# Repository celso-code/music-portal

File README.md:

# music-portal
- this is a project made for the fallout project on hack club, its called **music portal**. It is a (semi) 1 to 1 replica of the radio from the game portal, but its not just a replica, it is also a **fully functional FM radio AND a blutetooth speaker**, hence the name music portal .
- How do you build it ? Its pretty easy so the pcb fits in a slot in the black base part, and so does the black lid, the withe upper part has holes to intall 3 nuts which are also in the base, so just aling them, use a solder iron the place the nuts in each hole and use screws to join them together
- The way you use it pretty intuitive, theres a switch in the back to choose betweeen off, fm radio, and bluetooth, then theres two knobs, one to control the radio station if you're on radio mode and the other to control the volume.
- Its powwered by an ESP32 for the main control, for the fm functions it uses the fm radio module RDA5807 with a simple amplifier circuit for the speaker, and the it uses the MAX98357 as  DAC (digital to analog converter) for the bluetooth speaker mode.
- My reason to build this project is because portal is one of my favourite games oat and since the radio is one of the most iconic "symbols" of the game  I think it would be pretty cool to have it as physical object that also has a real purpose and utility. 
- I also tough it would be a cool way to learn certain skills  like cad modelling and pcb design 
heres a few photos of the project

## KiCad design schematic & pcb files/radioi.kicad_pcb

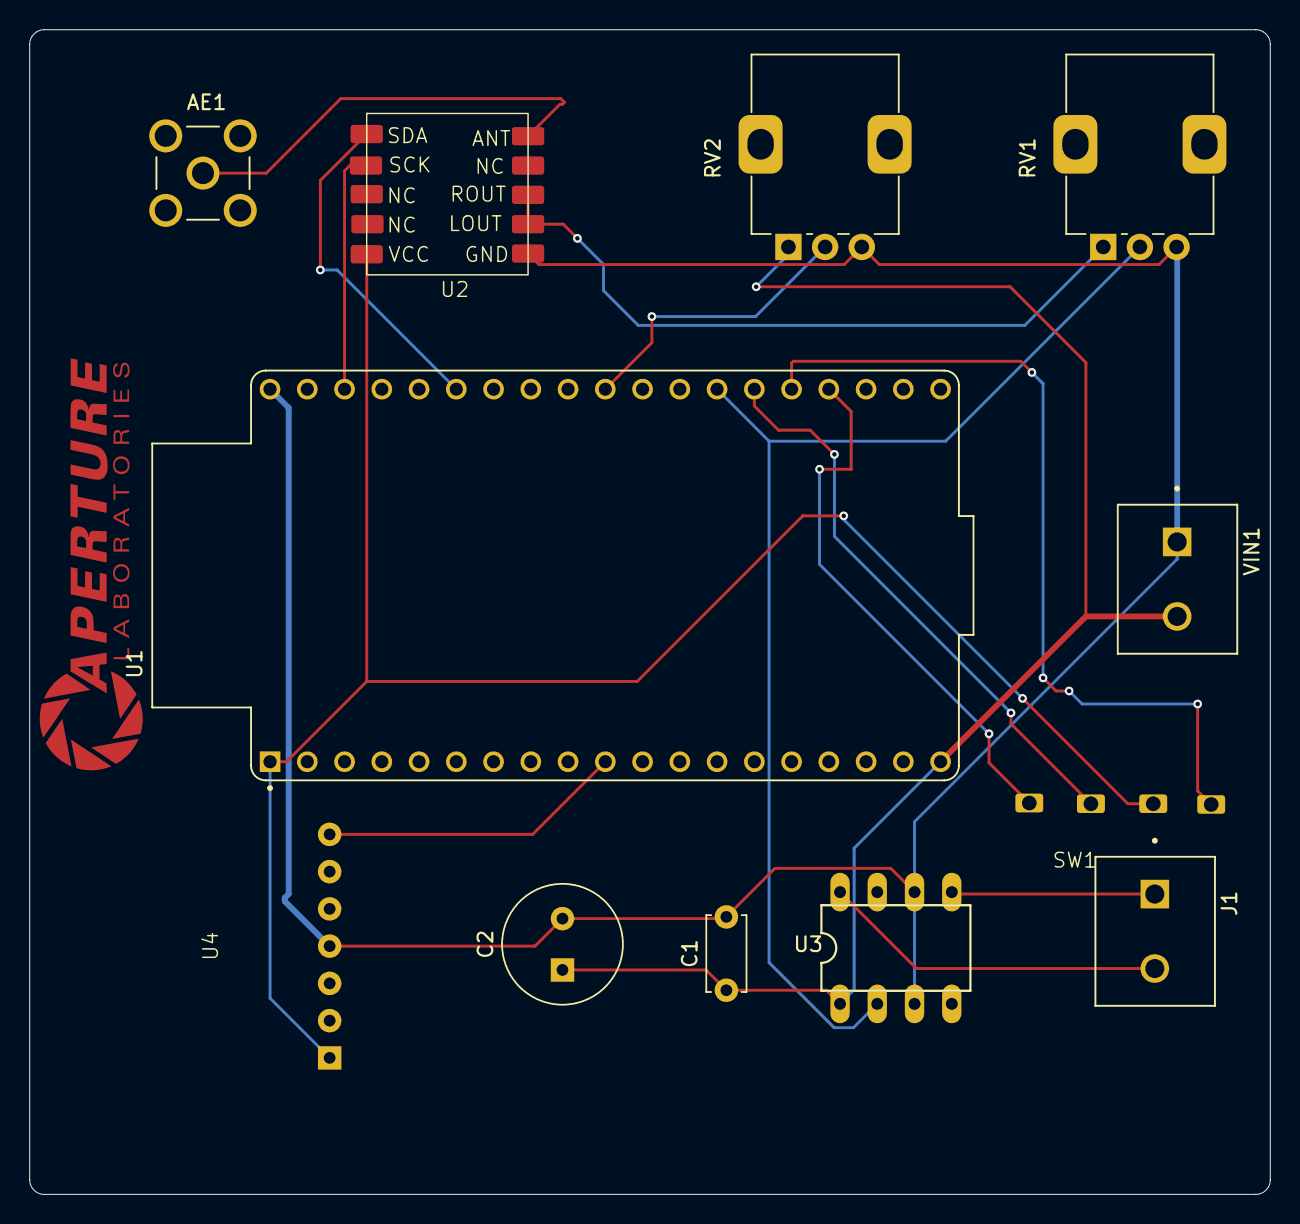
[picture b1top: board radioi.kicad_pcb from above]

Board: 2 copper layers, 84.6 x 79.4 mm, 12 parts (0 on the bottom side), 15 nets.

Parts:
AE1: Antenna; HUBER_SUHNER_82_SMA-50-0-41_133_NE
C1: 1uf; C_Disc_D5.0mm_W2.5mm_P5.00mm
C2: 100uF; C_Radial_D8.0mm_H11.5mm_P3.50mm_polar
J1: 1729128; PHOENIX_1729128
RV1: 5K; Potentiometer_Alps_RK09K_Single_Vertical
RV2: 5v; Potentiometer_Alps_RK09K_Single_Vertical
SW1: SW_DP3T; DP3T
U1: ESP32-DEVKITC-32E; MODULE_ESP32-DEVKITC-32E
U2: RDA5807M; RDA5807M-MY
U3: TDA7052A; DIL08
U4: MAX98357A; MAX98357
VIN1: 1729128; PHOENIX_1729128

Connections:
unnamed: AE1.1 (A), U2.6 (ANT)
unnamed: J1.1, U3.5
unnamed: J1.2, U3.8
unnamed: SW1.3, U1.J2_1 (3V3), U2.5 (VCC), U4.8 (VDD)
unnamed: C1.1, C2.1, RV2.1, U1.J2_19 (EXT_5V), U3.1 (VP), VIN1.2
unnamed: C1.2, C2.2, RV1.3, RV2.3, U1.J3_1 (GND_J3_1), U2.10 (GND), U3.3 (GND), U3.6 (GND), U4.11 (GND)
unnamed: SW1.2, U1.J3_14 (IO0)
unnamed: SW1.4, U1.J3_15 (IO2)
unnamed: RV1.2, U1.J3_13 (IO4), U3.2 (+)
unnamed: RV2.2, U1.J3_10 (IO5)
unnamed: SW1.1, U1.J3_16 (IO15)
unnamed: U1.J3_6 (IO21), U2.1 (SCA)
unnamed: U1.J3_3 (IO22), U2.4 (SCR)
unnamed: U1.J2_10 (IO26), U4.14 (LRCLK)
unnamed: RV1.1, U2.8 (LO), U2.9 (RO)

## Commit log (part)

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2026-05-13 Enhance README with project details and images
    Expanded project description with details about functionality, components, and personal motivation. Added images and schematic for better understanding.
2026-05-13 Refactor Arduino code with improved comments
    Updated comments for clarity and added missing include.
2026-05-13 pcb files
    these are the step and gerber files for the pcb
2026-05-17 Create 3D print files
2026-05-17 3d printable files
    these are the files for the 3d print
2026-05-21 Create temp
2026-05-21 Create t
2026-05-21 these files are to 3d print (duhh)
2026-05-21 Gerber Step an schematic
2026-05-21 Revise README with project details and images
    Updated project description and added images.
2026-05-21 bill of materials to build this project
2026-05-23 libraries for radio modules and amplifier
    you MIGTH need these
2026-05-23 schematic file
2026-05-24 these are the step files
2026-05-24 step files
2026-05-24 organizing images
    Updated image references and fixed typos in the README.
2026-05-24 organizing images again
    Added additional images to showcase the project.
2026-05-24 organizing images again
    Corrected typos and improved clarity in project description.
2026-05-24 this is the code ofr the project
2026-05-24 Update README with build instructions
    Added instructions for building the music portal project.
2026-05-25 Clean up image tags in README
    Removed duplicate image tags and adjusted formatting.
2026-05-25 step by satep intructuoins for assebly and bom
2026-05-25 thse are the actual pcb and schetch files
2026-05-25 Add Tinkercad model links
    Added links to Tinkercad models for reference.
2026-05-25 yo
    Added images and improved clarity in the build instructions.
2026-06-06 THIS THE HIGH QUALITY PDF
2026-06-17 updated the slot for the pcb
